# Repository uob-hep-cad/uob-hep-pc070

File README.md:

# uob-hep-pc070
Simple AIDAInnova DisplayPort to AIDA(-2020) HDMI connector

Converts from AIDAInnova fanout and TLU DisplayPort connector to AIDA(-2020) TLU HDMI connector.

Hierarchical design. pc070_aida_hdmi_dp is the toplevel. pc070_aida_hdmi_dp_single is a single DisplayPort / HDMI

Designed with KiCAD 6.0.4

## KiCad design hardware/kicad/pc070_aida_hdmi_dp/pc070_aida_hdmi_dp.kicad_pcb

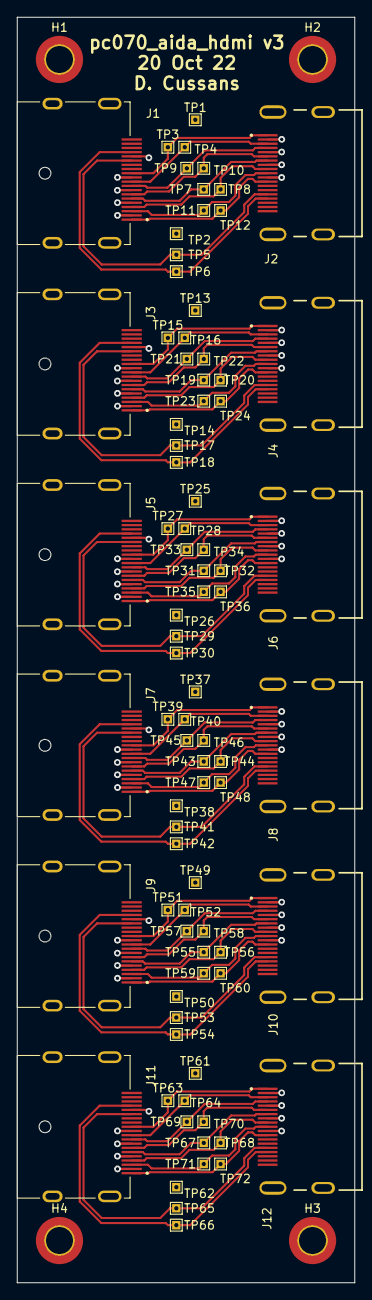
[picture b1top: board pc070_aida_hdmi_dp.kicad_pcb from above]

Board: 2 copper layers, 40.0 x 150.0 mm, 88 parts (0 on the bottom side), 61 nets.

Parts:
H1, H2, H3, H4: MountingHole_Pad; MountingHole_3.2mm_M3_DIN965_Pad_TopBottom
J1, J3, J5, J7, J9, J11: 47272-0001; MOLEX_47272-0001
J2, J4, J6, J8, J10, J12: HDMR-19-01-S-SM-TR; SAMTEC_HDMR-19-01-S-SM-TR
TP1, TP2, TP3, TP4, TP5, TP6, TP7, TP8, TP9, TP10, TP11, TP12, TP13, TP14, TP15, TP16, TP17, TP18, TP19, TP20, TP21, TP22, TP23, TP24, TP25, TP26, TP27, TP28, TP29, TP30, TP31, TP32, TP33, TP34, TP35, TP36, TP37, TP38, TP39, TP40, TP41, TP42, TP43, TP44, TP45, TP46, TP47, TP48, TP49, TP50, TP51, TP52, TP53, TP54, TP55, TP56, TP57, TP58, TP59, TP60, TP61, TP62, TP63, TP64, TP65, TP66, TP67, TP68, TP69, TP70, TP71, TP72: TestPoint; TestPoint_THTPad_1.0x1.0mm_Drill0.5mm

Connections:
/pc070_aida_hdmi_dp_single1/BUSY: J3.6, J4.07, TP19.1
/pc070_aida_hdmi_dp_single1/BUSY*: J3.4, J4.09, TP20.1
/pc070_aida_hdmi_dp_single1/CLK: J3.12, J4.01, TP15.1
/pc070_aida_hdmi_dp_single1/CLK*: J3.10, J4.03, TP16.1
/pc070_aida_hdmi_dp_single1/CONT: J3.9, J4.04, TP21.1
/pc070_aida_hdmi_dp_single1/CONT*: J3.7, J4.06, TP22.1
/pc070_aida_hdmi_dp_single1/SPARE: J3.3, J4.10, TP23.1
/pc070_aida_hdmi_dp_single1/SPARE*: J3.1, J4.12, TP24.1
/pc070_aida_hdmi_dp_single1/TRIG: J3.15, J4.15, TP17.1
/pc070_aida_hdmi_dp_single1/TRIG*: J3.17, J4.16, TP18.1
/pc070_aida_hdmi_dp_single2/BUSY: J5.6, J6.07, TP31.1
/pc070_aida_hdmi_dp_single2/BUSY*: J5.4, J6.09, TP32.1
/pc070_aida_hdmi_dp_single2/CLK: J5.12, J6.01, TP27.1
/pc070_aida_hdmi_dp_single2/CLK*: J5.10, J6.03, TP28.1
/pc070_aida_hdmi_dp_single2/CONT: J5.9, J6.04, TP33.1
/pc070_aida_hdmi_dp_single2/CONT*: J5.7, J6.06, TP34.1
/pc070_aida_hdmi_dp_single2/SPARE: J5.3, J6.10, TP35.1
/pc070_aida_hdmi_dp_single2/SPARE*: J5.1, J6.12, TP36.1
/pc070_aida_hdmi_dp_single2/TRIG: J5.15, J6.15, TP29.1
/pc070_aida_hdmi_dp_single2/TRIG*: J5.17, J6.16, TP30.1
/pc070_aida_hdmi_dp_single3/BUSY: J11.6, J12.07, TP67.1
/pc070_aida_hdmi_dp_single3/BUSY*: J11.4, J12.09, TP68.1
/pc070_aida_hdmi_dp_single3/CLK: J11.12, J12.01, TP63.1
/pc070_aida_hdmi_dp_single3/CLK*: J11.10, J12.03, TP64.1
/pc070_aida_hdmi_dp_single3/CONT: J11.9, J12.04, TP69.1
/pc070_aida_hdmi_dp_single3/CONT*: J11.7, J12.06, TP70.1
/pc070_aida_hdmi_dp_single3/SPARE: J11.3, J12.10, TP71.1
/pc070_aida_hdmi_dp_single3/SPARE*: J11.1, J12.12, TP72.1
/pc070_aida_hdmi_dp_single3/TRIG: J11.15, J12.15, TP65.1
/pc070_aida_hdmi_dp_single3/TRIG*: J11.17, J12.16, TP66.1
/pc070_aida_hdmi_dp_single4/BUSY: J9.6, J10.07, TP55.1
/pc070_aida_hdmi_dp_single4/BUSY*: J9.4, J10.09, TP56.1
/pc070_aida_hdmi_dp_single4/CLK: J9.12, J10.01, TP51.1
/pc070_aida_hdmi_dp_single4/CLK*: J9.10, J10.03, TP52.1
/pc070_aida_hdmi_dp_single4/CONT: J9.9, J10.04, TP57.1
/pc070_aida_hdmi_dp_single4/CONT*: J9.7, J10.06, TP58.1
/pc070_aida_hdmi_dp_single4/SPARE: J9.3, J10.10, TP59.1
/pc070_aida_hdmi_dp_single4/SPARE*: J9.1, J10.12, TP60.1
/pc070_aida_hdmi_dp_single4/TRIG: J9.15, J10.15, TP53.1
/pc070_aida_hdmi_dp_single4/TRIG*: J9.17, J10.16, TP54.1
/pc070_aida_hdmi_dp_single5/BUSY: J7.6, J8.07, TP43.1
/pc070_aida_hdmi_dp_single5/BUSY*: J7.4, J8.09, TP44.1
/pc070_aida_hdmi_dp_single5/CLK: J7.12, J8.01, TP39.1
/pc070_aida_hdmi_dp_single5/CLK*: J7.10, J8.03, TP40.1
/pc070_aida_hdmi_dp_single5/CONT: J7.9, J8.04, TP45.1
/pc070_aida_hdmi_dp_single5/CONT*: J7.7, J8.06, TP46.1
/pc070_aida_hdmi_dp_single5/SPARE: J7.3, J8.10, TP47.1
/pc070_aida_hdmi_dp_single5/SPARE*: J7.1, J8.12, TP48.1
/pc070_aida_hdmi_dp_single5/TRIG: J7.15, J8.15, TP41.1
/pc070_aida_hdmi_dp_single5/TRIG*: J7.17, J8.16, TP42.1
/pc070_aida_hdmi_dp_single/BUSY: J1.6, J2.07, TP7.1
/pc070_aida_hdmi_dp_single/BUSY*: J1.4, J2.09, TP8.1
/pc070_aida_hdmi_dp_single/CLK: J1.12, J2.01, TP3.1
/pc070_aida_hdmi_dp_single/CLK*: J1.10, J2.03, TP4.1
/pc070_aida_hdmi_dp_single/CONT: J1.9, J2.04, TP9.1
/pc070_aida_hdmi_dp_single/CONT*: J1.7, J2.06, TP10.1
/pc070_aida_hdmi_dp_single/SPARE: J1.3, J2.10, TP11.1
/pc070_aida_hdmi_dp_single/SPARE*: J1.1, J2.12, TP12.1
/pc070_aida_hdmi_dp_single/TRIG: J1.15, J2.15, TP5.1
/pc070_aida_hdmi_dp_single/TRIG*: J1.17, J2.16, TP6.1
GND: H1.1, H2.1, H3.1, H4.1, J1.2, J1.5, J1.8, J1.11, J1.16, J1.S1 (SHIELD), J1.S2 (SHIELD), J1.S3 (SHIELD), J1.S4 (SHIELD), J2.02, J2.05, J2.08, J2.11, J2.S1 (SHIELD), J2.S2 (SHIELD), J2.S3 (SHIELD), J2.S4 (SHIELD), J3.2, J3.5, J3.8, J3.11, J3.16, J3.S1 (SHIELD), J3.S2 (SHIELD), J3.S3 (SHIELD), J3.S4 (SHIELD), J4.02, J4.05, J4.08, J4.11, J4.S1 (SHIELD), J4.S2 (SHIELD), J4.S3 (SHIELD), J4.S4 (SHIELD), J5.2, J5.5, J5.8, J5.11, J5.16, J5.S1 (SHIELD), J5.S2 (SHIELD), J5.S3 (SHIELD), J5.S4 (SHIELD), J6.02, J6.05, J6.08, J6.11, J6.S1 (SHIELD), J6.S2 (SHIELD), J6.S3 (SHIELD), J6.S4 (SHIELD), J7.2, J7.5, J7.8, J7.11, J7.16, J7.S1 (SHIELD), J7.S2 (SHIELD), J7.S3 (SHIELD), J7.S4 (SHIELD), J8.02, J8.05, J8.08, J8.11, J8.S1 (SHIELD), J8.S2 (SHIELD), J8.S3 (SHIELD), J8.S4 (SHIELD), J9.2, J9.5, J9.8, J9.11, J9.16, J9.S1 (SHIELD), J9.S2 (SHIELD), J9.S3 (SHIELD), J9.S4 (SHIELD), J10.02, J10.05, J10.08, J10.11, J10.S1 (SHIELD), J10.S2 (SHIELD), J10.S3 (SHIELD), J10.S4 (SHIELD), J11.2, J11.5, J11.8, J11.11, J11.16, J11.S1 (SHIELD), J11.S2 (SHIELD), J11.S3 (SHIELD), J11.S4 (SHIELD), J12.02, J12.05, J12.08, J12.11, J12.S1 (SHIELD), J12.S2 (SHIELD), J12.S3 (SHIELD), J12.S4 (SHIELD), TP1.1, TP2.1, TP13.1, TP14.1, TP25.1, TP26.1, TP37.1, TP38.1, TP49.1, TP50.1, TP61.1, TP62.1

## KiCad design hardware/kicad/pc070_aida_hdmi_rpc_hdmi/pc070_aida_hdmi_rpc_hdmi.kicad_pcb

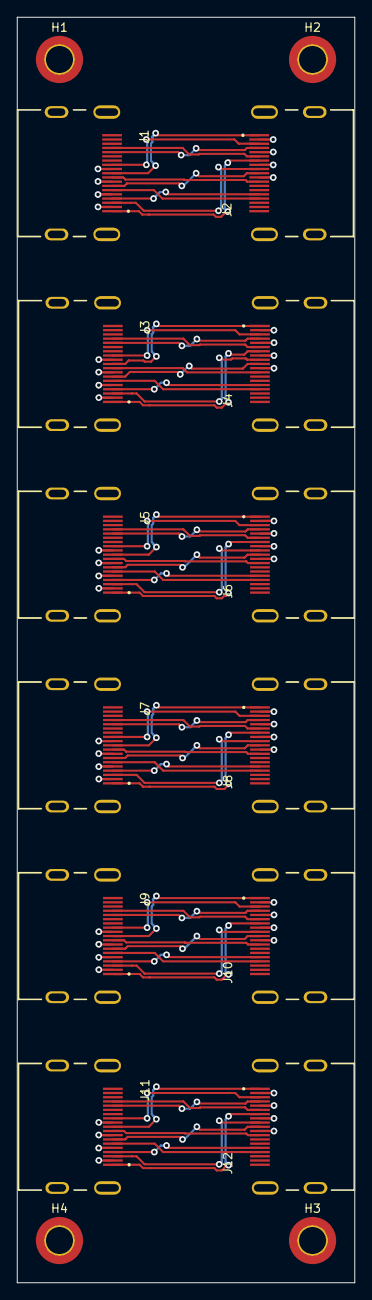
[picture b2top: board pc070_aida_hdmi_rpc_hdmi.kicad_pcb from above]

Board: 4 copper layers, 40.0 x 150.0 mm, 16 parts (0 on the bottom side), 61 nets.

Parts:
H1, H2, H3, H4: MountingHole_Pad; MountingHole_3.2mm_M3_DIN965_Pad_TopBottom
J1, J2, J3, J4, J5, J6, J7, J8, J9, J10, J11, J12: HDMR-19-01-S-SM-TR; SAMTEC_HDMR-19-01-S-SM-TR

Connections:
/pc070_aida_hdmi_rpc_hdmi_single1/BUSY: J3.01, J4.07
/pc070_aida_hdmi_rpc_hdmi_single1/BUSY*: J3.03, J4.09
/pc070_aida_hdmi_rpc_hdmi_single1/CLK: J3.10, J4.01
/pc070_aida_hdmi_rpc_hdmi_single1/CLK*: J3.12, J4.03
/pc070_aida_hdmi_rpc_hdmi_single1/CONT: J3.15, J4.04
/pc070_aida_hdmi_rpc_hdmi_single1/CONT*: J3.16, J4.06
/pc070_aida_hdmi_rpc_hdmi_single1/SPARE: J3.07, J4.10
/pc070_aida_hdmi_rpc_hdmi_single1/SPARE*: J3.09, J4.12
/pc070_aida_hdmi_rpc_hdmi_single1/TRIG: J3.04, J4.15
/pc070_aida_hdmi_rpc_hdmi_single1/TRIG*: J3.06, J4.16
/pc070_aida_hdmi_rpc_hdmi_single2/BUSY: J5.01, J6.07
/pc070_aida_hdmi_rpc_hdmi_single2/BUSY*: J5.03, J6.09
/pc070_aida_hdmi_rpc_hdmi_single2/CLK: J5.10, J6.01
/pc070_aida_hdmi_rpc_hdmi_single2/CLK*: J5.12, J6.03
/pc070_aida_hdmi_rpc_hdmi_single2/CONT: J5.15, J6.04
/pc070_aida_hdmi_rpc_hdmi_single2/CONT*: J5.16, J6.06
/pc070_aida_hdmi_rpc_hdmi_single2/SPARE: J5.07, J6.10
/pc070_aida_hdmi_rpc_hdmi_single2/SPARE*: J5.09, J6.12
/pc070_aida_hdmi_rpc_hdmi_single2/TRIG: J5.04, J6.15
/pc070_aida_hdmi_rpc_hdmi_single2/TRIG*: J5.06, J6.16
/pc070_aida_hdmi_rpc_hdmi_single3/BUSY: J11.01, J12.07
/pc070_aida_hdmi_rpc_hdmi_single3/BUSY*: J11.03, J12.09
/pc070_aida_hdmi_rpc_hdmi_single3/CLK: J11.10, J12.01
/pc070_aida_hdmi_rpc_hdmi_single3/CLK*: J11.12, J12.03
/pc070_aida_hdmi_rpc_hdmi_single3/CONT: J11.15, J12.04
/pc070_aida_hdmi_rpc_hdmi_single3/CONT*: J11.16, J12.06
/pc070_aida_hdmi_rpc_hdmi_single3/SPARE: J11.07, J12.10
/pc070_aida_hdmi_rpc_hdmi_single3/SPARE*: J11.09, J12.12
/pc070_aida_hdmi_rpc_hdmi_single3/TRIG: J11.04, J12.15
/pc070_aida_hdmi_rpc_hdmi_single3/TRIG*: J11.06, J12.16
/pc070_aida_hdmi_rpc_hdmi_single4/BUSY: J7.01, J8.07
/pc070_aida_hdmi_rpc_hdmi_single4/BUSY*: J7.03, J8.09
/pc070_aida_hdmi_rpc_hdmi_single4/CLK: J7.10, J8.01
/pc070_aida_hdmi_rpc_hdmi_single4/CLK*: J7.12, J8.03
/pc070_aida_hdmi_rpc_hdmi_single4/CONT: J7.15, J8.04
/pc070_aida_hdmi_rpc_hdmi_single4/CONT*: J7.16, J8.06
/pc070_aida_hdmi_rpc_hdmi_single4/SPARE: J7.07, J8.10
/pc070_aida_hdmi_rpc_hdmi_single4/SPARE*: J7.09, J8.12
/pc070_aida_hdmi_rpc_hdmi_single4/TRIG: J7.04, J8.15
/pc070_aida_hdmi_rpc_hdmi_single4/TRIG*: J7.06, J8.16
/pc070_aida_hdmi_rpc_hdmi_single5/BUSY: J9.01, J10.07
/pc070_aida_hdmi_rpc_hdmi_single5/BUSY*: J9.03, J10.09
/pc070_aida_hdmi_rpc_hdmi_single5/CLK: J9.10, J10.01
/pc070_aida_hdmi_rpc_hdmi_single5/CLK*: J9.12, J10.03
/pc070_aida_hdmi_rpc_hdmi_single5/CONT: J9.15, J10.04
/pc070_aida_hdmi_rpc_hdmi_single5/CONT*: J9.16, J10.06
/pc070_aida_hdmi_rpc_hdmi_single5/SPARE: J9.07, J10.10
/pc070_aida_hdmi_rpc_hdmi_single5/SPARE*: J9.09, J10.12
/pc070_aida_hdmi_rpc_hdmi_single5/TRIG: J9.04, J10.15
/pc070_aida_hdmi_rpc_hdmi_single5/TRIG*: J9.06, J10.16
/pc070_aida_hdmi_rpc_hdmi_single/BUSY: J1.01, J2.07
/pc070_aida_hdmi_rpc_hdmi_single/BUSY*: J1.03, J2.09
/pc070_aida_hdmi_rpc_hdmi_single/CLK: J1.10, J2.01
/pc070_aida_hdmi_rpc_hdmi_single/CLK*: J1.12, J2.03
/pc070_aida_hdmi_rpc_hdmi_single/CONT: J1.15, J2.04
/pc070_aida_hdmi_rpc_hdmi_single/CONT*: J1.16, J2.06
/pc070_aida_hdmi_rpc_hdmi_single/SPARE: J1.07, J2.10
/pc070_aida_hdmi_rpc_hdmi_single/SPARE*: J1.09, J2.12
/pc070_aida_hdmi_rpc_hdmi_single/TRIG: J1.04, J2.15
/pc070_aida_hdmi_rpc_hdmi_single/TRIG*: J1.06, J2.16
GND: H1.1, H2.1, H3.1, H4.1, J1.02, J1.05, J1.08, J1.11, J1.S1 (SHIELD), J1.S2 (SHIELD), J1.S3 (SHIELD), J1.S4 (SHIELD), J2.02, J2.05, J2.08, J2.11, J2.S1 (SHIELD), J2.S2 (SHIELD), J2.S3 (SHIELD), J2.S4 (SHIELD), J3.02, J3.05, J3.08, J3.11, J3.S1 (SHIELD), J3.S2 (SHIELD), J3.S3 (SHIELD), J3.S4 (SHIELD), J4.02, J4.05, J4.08, J4.11, J4.S1 (SHIELD), J4.S2 (SHIELD), J4.S3 (SHIELD), J4.S4 (SHIELD), J5.02, J5.05, J5.08, J5.11, J5.S1 (SHIELD), J5.S2 (SHIELD), J5.S3 (SHIELD), J5.S4 (SHIELD), J6.02, J6.05, J6.08, J6.11, J6.S1 (SHIELD), J6.S2 (SHIELD), J6.S3 (SHIELD), J6.S4 (SHIELD), J7.02, J7.05, J7.08, J7.11, J7.S1 (SHIELD), J7.S2 (SHIELD), J7.S3 (SHIELD), J7.S4 (SHIELD), J8.02, J8.05, J8.08, J8.11, J8.S1 (SHIELD), J8.S2 (SHIELD), J8.S3 (SHIELD), J8.S4 (SHIELD), J9.02, J9.05, J9.08, J9.11, J9.S1 (SHIELD), J9.S2 (SHIELD), J9.S3 (SHIELD), J9.S4 (SHIELD), J10.02, J10.05, J10.08, J10.11, J10.S1 (SHIELD), J10.S2 (SHIELD), J10.S3 (SHIELD), J10.S4 (SHIELD), J11.02, J11.05, J11.08, J11.11, J11.S1 (SHIELD), J11.S2 (SHIELD), J11.S3 (SHIELD), J11.S4 (SHIELD), J12.02, J12.05, J12.08, J12.11, J12.S1 (SHIELD), J12.S2 (SHIELD), J12.S3 (SHIELD), J12.S4 (SHIELD)

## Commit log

2022-07-15 Design files for AIDA Display Port <--> AIDA HDMI
2022-07-15 Minor tidying of artwork
2022-07-20 Copied pc070_aida_hdmi_dp{,_single} to pc070_aida_hdmi_rpc_hdmi{,_single} and used as a starting point for PCB to map early RPC fanout to AIDA(2020) TLU HDMI connector
2022-07-26 Tweaked 3D model alignment on HDMI connector
2022-08-08 Adding manufacturing artwork
2022-08-08 Committing manufacturing artwork
2022-08-24 COnverting BOM to XLXS
2022-09-30 Checking in design files for incorrect pinout DP design
2022-09-30 Producing artwork for bug-fixed bodge board
2022-11-01 Committing artwork for v3 of the adaptor board
2023-12-04 Adding Zip archives and schematics
